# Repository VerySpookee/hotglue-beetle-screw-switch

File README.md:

# hotglue-beetle-screw-switch
Combat robot power switch design for use in a beetleweight robot.

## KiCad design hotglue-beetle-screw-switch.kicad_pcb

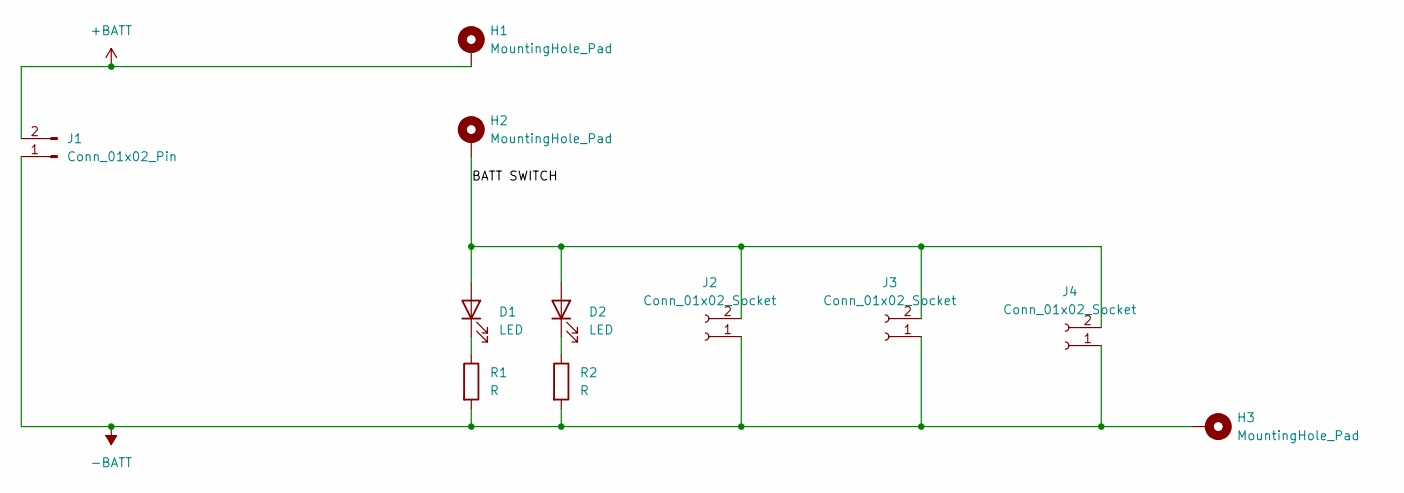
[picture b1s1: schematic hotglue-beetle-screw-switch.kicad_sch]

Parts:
D1, D2: LED; D_0603_1608Metric_Pad1.05x0.95mm_HandSolder
H1: MountingHole_Pad; Wurth-M3-screw-contact
H2, H3: MountingHole_Pad; MP_Wurth_WP-SMBU_746600330
J1: Conn_01x02_Pin; AMASS_XT30U-M_1x02_P5.0mm_Vertical
J2, J3, J4: Conn_01x02_Socket; AMASS_XT30U-F_1x02_P5.0mm_Vertical
R1, R2: R; R_0603_1608Metric_Pad0.98x0.95mm_HandSolder

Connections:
+BATT: H1.1 (1_1), J1.2
-BATT: H3.1 (1_1), J1.1, J2.1, J3.1, J4.1, R1.2, R2.2
/BATT SWITCH: D1.2 (A), D2.2 (A), H2.1 (1_1), J2.2, J3.2, J4.2
unnamed: D1.1 (K), R1.1
unnamed: D2.1 (K), R2.1

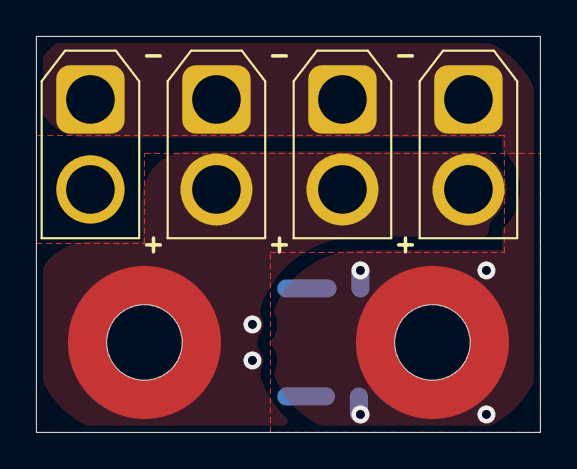
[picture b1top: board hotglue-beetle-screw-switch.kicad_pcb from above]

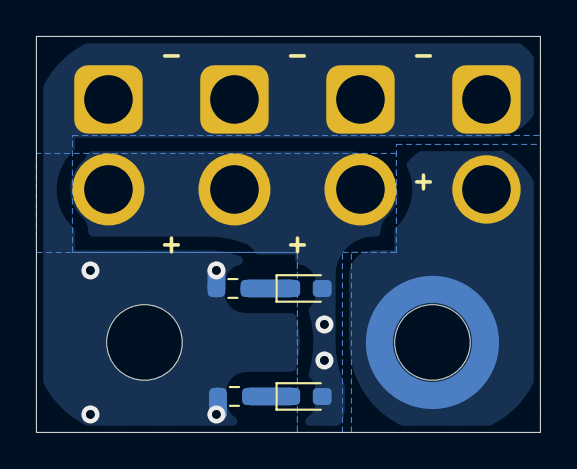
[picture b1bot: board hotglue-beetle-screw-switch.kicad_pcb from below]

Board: 2 copper layers, 28.0 x 22.0 mm, 11 parts (5 on the bottom side), 5 nets.
